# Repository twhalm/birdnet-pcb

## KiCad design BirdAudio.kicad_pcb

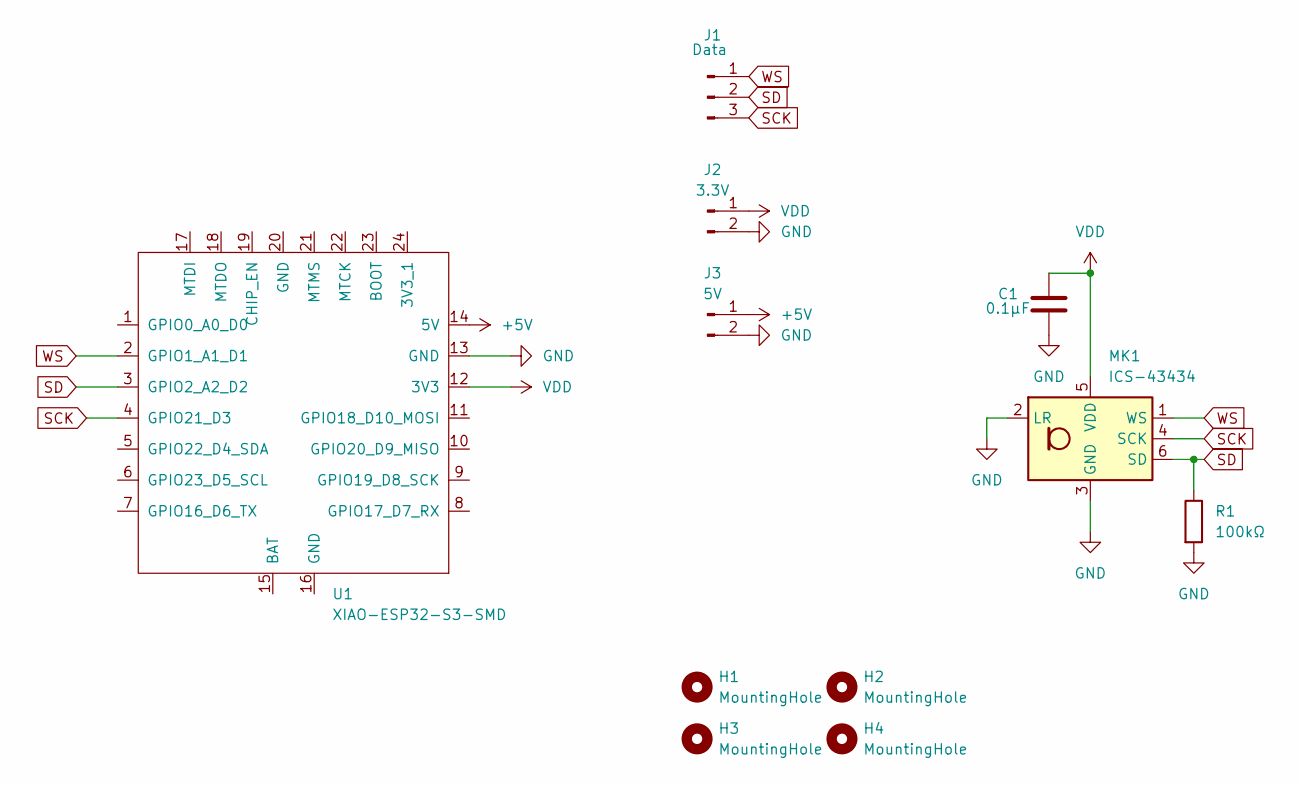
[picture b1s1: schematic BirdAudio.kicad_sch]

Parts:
C1: 0.1µF; C_0603_1608Metric; MPN GMC10X7R104K25NT
H1, H2, H3, H4: MountingHole; MountingHole_2.7mm_M2.5
J1: Data; JST_PH_B3B-PH-K_1x03_P2.00mm_Vertical; MPN B3B-PH-K-S
J2: 3.3V; JST_PH_B2B-PH-K_1x02_P2.00mm_Vertical; MPN B2B-PH-K-S
J3: 5V; JST_PH_B2B-PH-K_1x02_P2.00mm_Vertical; MPN B2B-PH-K-S
MK1: ICS-43434; InvenSense_ICS-43434-6_3.5x2.65mm; MPN ICS-43434
R1: 100kΩ; R_0603_1608Metric; MPN RMCF0603FT100K
U1: XIAO-ESP32-S3-SMD; XIAO-ESP32C6-SMD

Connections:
+5V: J3.1, U1.14 (5V)
GND: C1.2, J2.2, J3.2, MK1.2 (LR), MK1.3 (GND), R1.2, U1.13 (GND)
SCK: J1.3, MK1.4 (SCK), U1.4 (GPIO21_D3)
SD: J1.2, MK1.6 (SD), R1.1, U1.3 (GPIO2_A2_D2)
VDD: C1.1, J2.1, MK1.5 (VDD), U1.12 (3V3)
WS: J1.1, MK1.1 (WS), U1.2 (GPIO1_A1_D1)

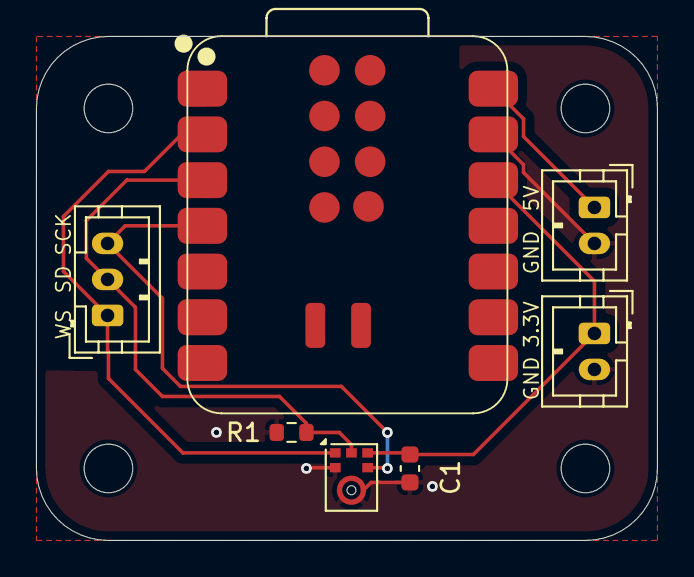
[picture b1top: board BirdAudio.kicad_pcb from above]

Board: 2 copper layers, 34.5 x 28.0 mm, 11 parts (0 on the bottom side), 6 nets.
